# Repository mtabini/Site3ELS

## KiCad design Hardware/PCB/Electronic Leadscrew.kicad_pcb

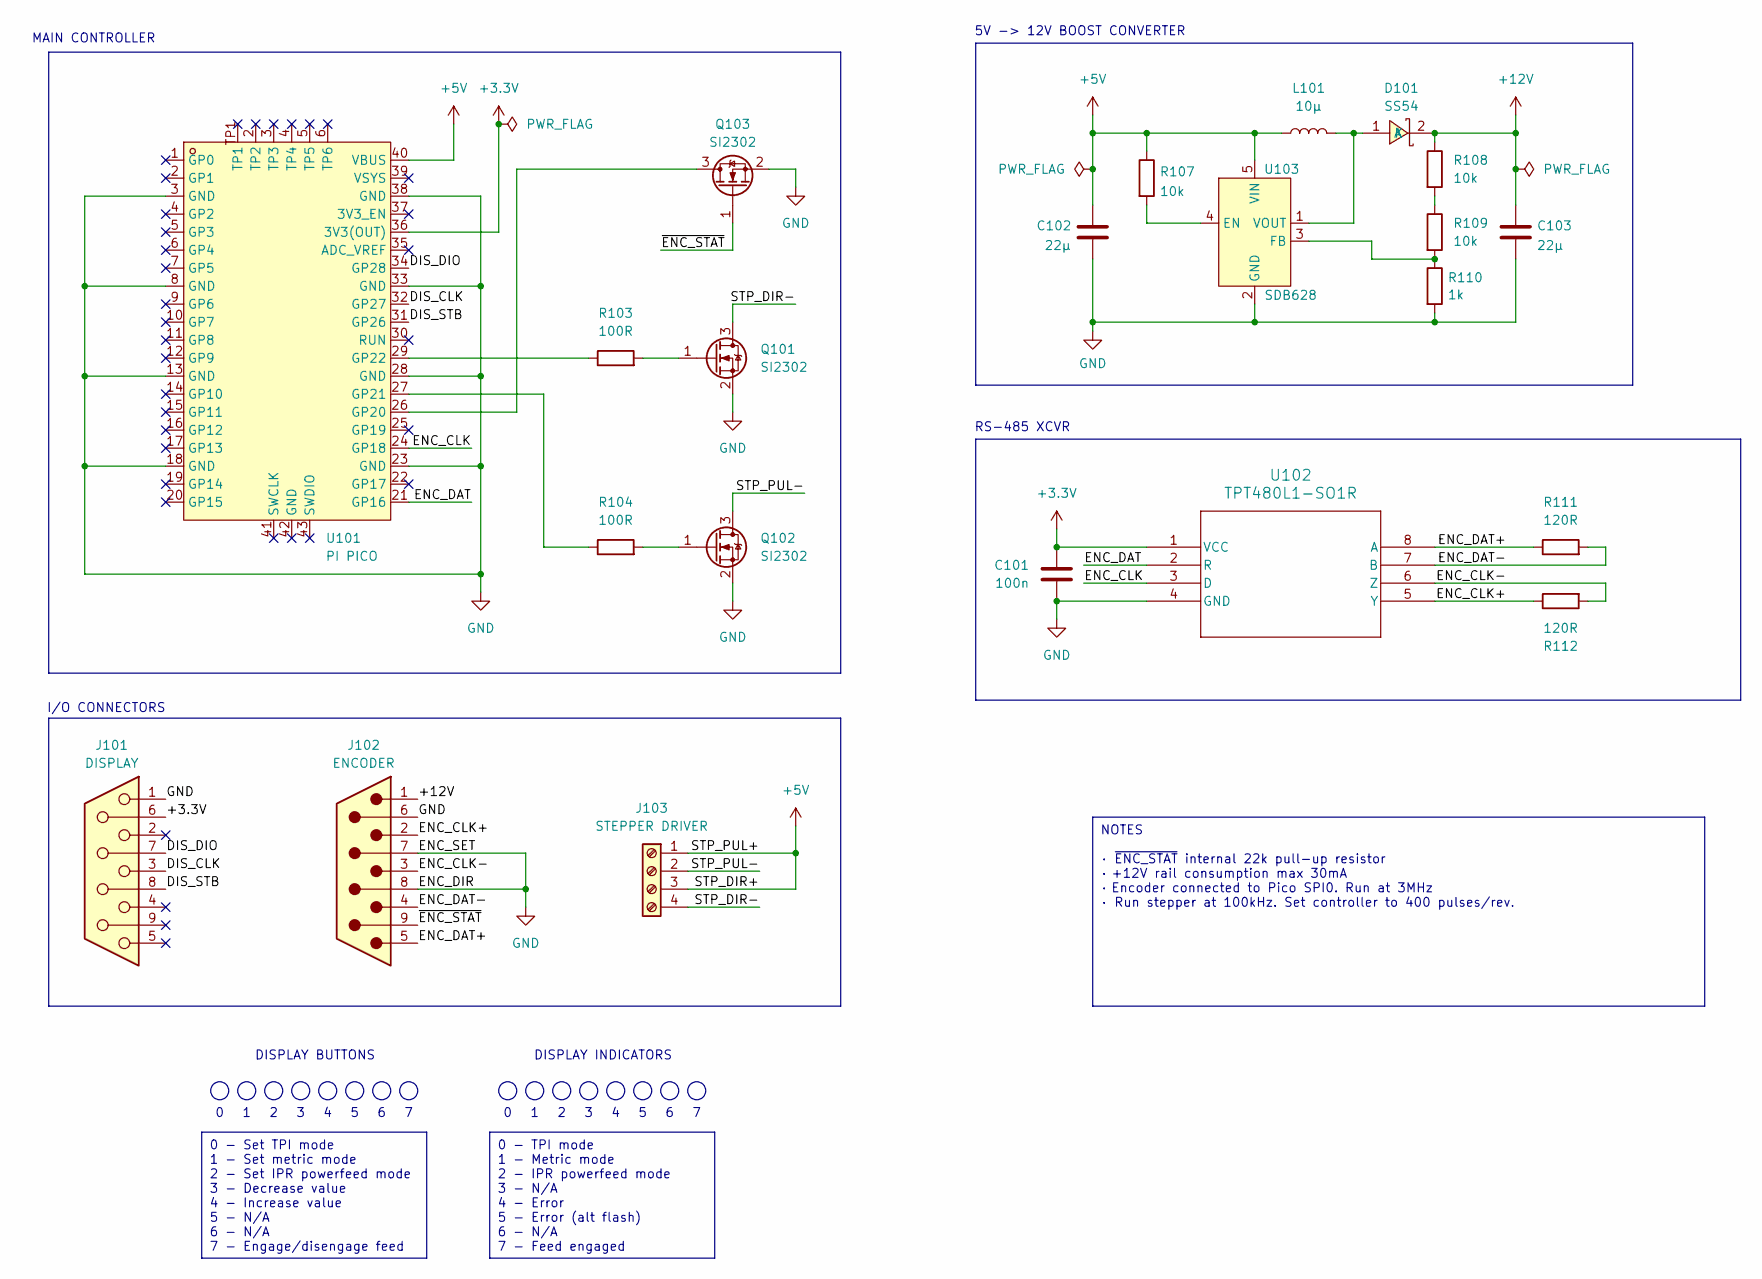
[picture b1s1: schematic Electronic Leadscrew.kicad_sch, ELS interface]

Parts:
C101: 100n; C_1206_3216Metric_Pad1.33x1.80mm_HandSolder; MPN C15008
C102, C103: 22µ; C_1206_3216Metric_Pad1.33x1.80mm_HandSolder
D101: SS54; SMA_L4.4-W2.8-LS5.4-R-RD; LCSC Part C22452
J101: DISPLAY; DSUB-9_Female_Horizontal_P2.77x2.84mm_EdgePinOffset7.70mm_H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
J102: ENCODER; DSUB-9_Male_Horizontal_P2.77x2.84mm_EdgePinOffset7.70mm_Hou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
J103: STEPPER DRIVER; TerminalBlock_4Ucon_1x04_P3.50mm_Horizontal
L101: 10µ; L_6.3x6.3_H3
Q101, Q102, Q103: SI2302; SOT-23_Handsoldering
R103, R104: 100R; R_1206_3216Metric_Pad1.30x1.75mm_HandSolder; MPN C17901
R107: 10k; R_1206_3216Metric_Pad1.30x1.75mm_HandSolder
R108, R109: 10k; R_1206_3216Metric_Pad1.30x1.75mm_HandSolder; MPN C17902
R110: 1k; R_1206_3216Metric_Pad1.30x1.75mm_HandSolder; MPN C4410
R111, R112: 120R; R_1206_3216Metric_Pad1.30x1.75mm_HandSolder
U101: PI PICO; COMM-SMD_L51.0-W21.0-P2.54_SC0916; LCSC Part C7203002
U102: TPT480L1-SO1R; SO1SOP-8-A_TPK
U103: SDB628; SOT-23-6_Handsoldering

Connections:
+3.3V: C101.1, J101.6, U101.36 (3V3(OUT)), U102.1 (VCC)
+5V: C102.1, J103.1, J103.3, L101.1, R107.1, U101.40 (VBUS), U103.5 (VIN)
+12V: C103.1, D101.2 (K), J102.1, R108.1
/DIS_CLK: J101.3, U101.32 (GP27)
/DIS_DIO: J101.7, U101.34 (GP28)
/DIS_STB: J101.8, U101.31 (GP26)
/ENC_CLK: U101.24 (GP18), U102.3 (D)
/ENC_CLK+: J102.2, R112.1, U102.5 (Y)
/ENC_CLK-: J102.3, R112.2, U102.6 (Z)
/ENC_DAT: U101.21 (GP16), U102.2 (R)
/ENC_DAT+: J102.5, R111.1, U102.8 (A)
/ENC_DAT-: J102.4, R111.2, U102.7 (B)
/STP_DIR-: J103.4, Q101.3 (D)
/STP_PUL-: J103.2, Q102.3 (D)
/~ENC_STAT: J102.9, Q103.1 (G)
GND: C101.2, C102.2, C103.2, J101.1, J102.6, J102.7, J102.8, Q101.2 (S), Q102.2 (S), Q103.2 (S), R110.2, U101.3 (GND), U101.8 (GND), U101.13 (GND), U101.18 (GND), U101.23 (GND), U101.28 (GND), U101.33 (GND), U101.38 (GND), U102.4 (GND), U103.2 (GND)
unnamed: D101.1 (A), L101.2, U103.1 (VOUT)
unnamed: Q101.1 (G), R103.2
unnamed: Q102.1 (G), R104.2
unnamed: Q103.3 (D), U101.26 (GP20)
unnamed: R108.2, R109.1
unnamed: R104.1, U101.27 (GP21)
unnamed: R103.1, U101.29 (GP22)
unnamed: R107.2, U103.4 (EN)
unnamed: R109.2, R110.1, U103.3 (FB)

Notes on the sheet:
0 - TPI mode 1 - Metric mode 2 - IPR powerfeed mode 3 - N/A 4 - Error 5 - Error (alt flash) 6 - N/A 7 - Feed engaged
NOTES · ~{ENC_STAT} internal 22k pull-up resistor · +12V rail consumption max 30mA · Encoder connected to Pico SPI0. Run at 3MHz · Run stepper at 100kHz. Set controller to 400 pulses/rev.
0 - Set TPI mode 1 - Set metric mode 2 - Set IPR powerfeed mode 3 - Decrease value 4 - Increase value 5 - N/A 6 - N/A 7 - Engage/disengage feed
MAIN CONTROLLER
DISPLAY INDICATORS
DISPLAY BUTTONS
5V -> 12V BOOST CONVERTER
I/O CONNECTORS
RS-485 XCVR

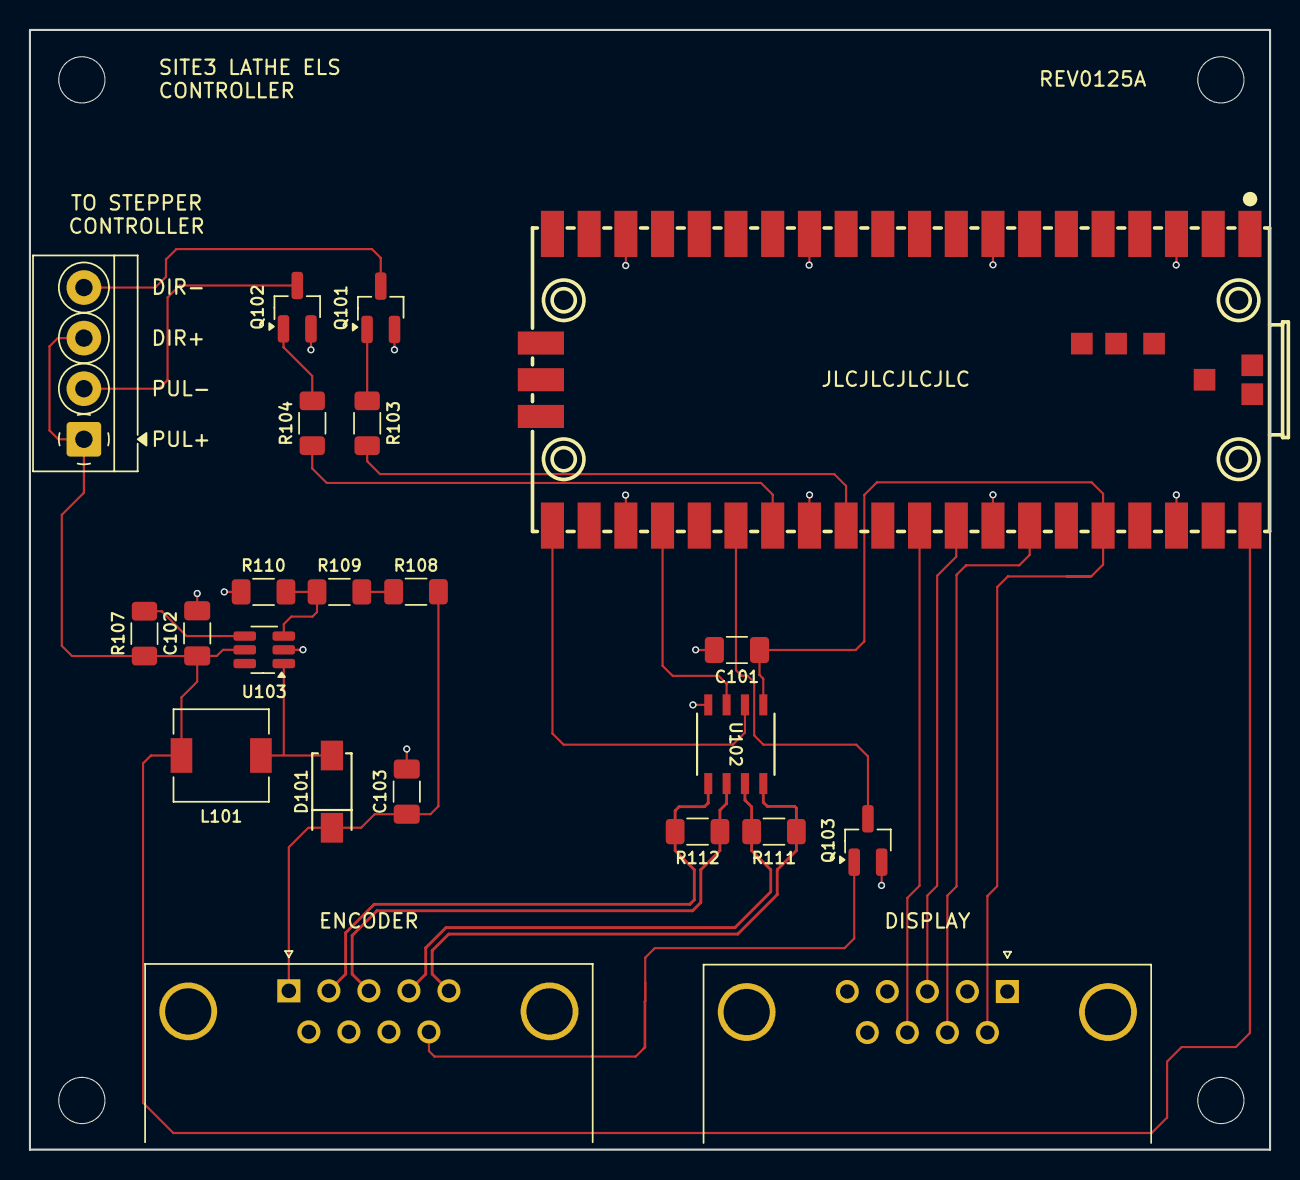
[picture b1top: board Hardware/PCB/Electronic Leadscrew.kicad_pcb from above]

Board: 2 copper layers, 85.8 x 77.5 mm, 22 parts (0 on the bottom side), 25 nets.

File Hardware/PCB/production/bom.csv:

Designator,Footprint,Quantity,Value,LCSC Part #
C101,1206,1,100n,C15008
"C102, C103",1206,2,22µ,
D101,SMA_L4.4-W2.8-LS5.4-R-RD,1,SS54,C22452
J101,DSUB-9_Female_Horizontal_P2.77x2.84mm_EdgePinOffset7.70mm_Housed_MountingHolesOffset9.12mm,1,DISPLAY,
J102,DSUB-9_Male_Horizontal_P2.77x2.84mm_EdgePinOffset7.70mm_Housed_MountingHolesOffset9.12mm,1,ENCODER,
J103,TerminalBlock_4Ucon_1x04_P3.50mm_Horizontal,1,STEPPER DRIVER,
L101,L_6.3x6.3_H3,1,10µ,
"Q101, Q102, Q103",SOT-23_Handsoldering,3,SI2302,
"R103, R104",1206,2,100R,C17901
R107,1206,1,10k,
"R108, R109",1206,2,10k,C17902
R110,1206,1,1k,C4410
"R111, R112",1206,2,120R,
U101,COMM-SMD_L51.0-W21.0-P2.54_SC0916,1,PI PICO,C7203002
U102,SO1SOP-8-A_TPK,1,TPT480L1-SO1R,
U103,SOT-23-6_Handsoldering,1,SDB628,

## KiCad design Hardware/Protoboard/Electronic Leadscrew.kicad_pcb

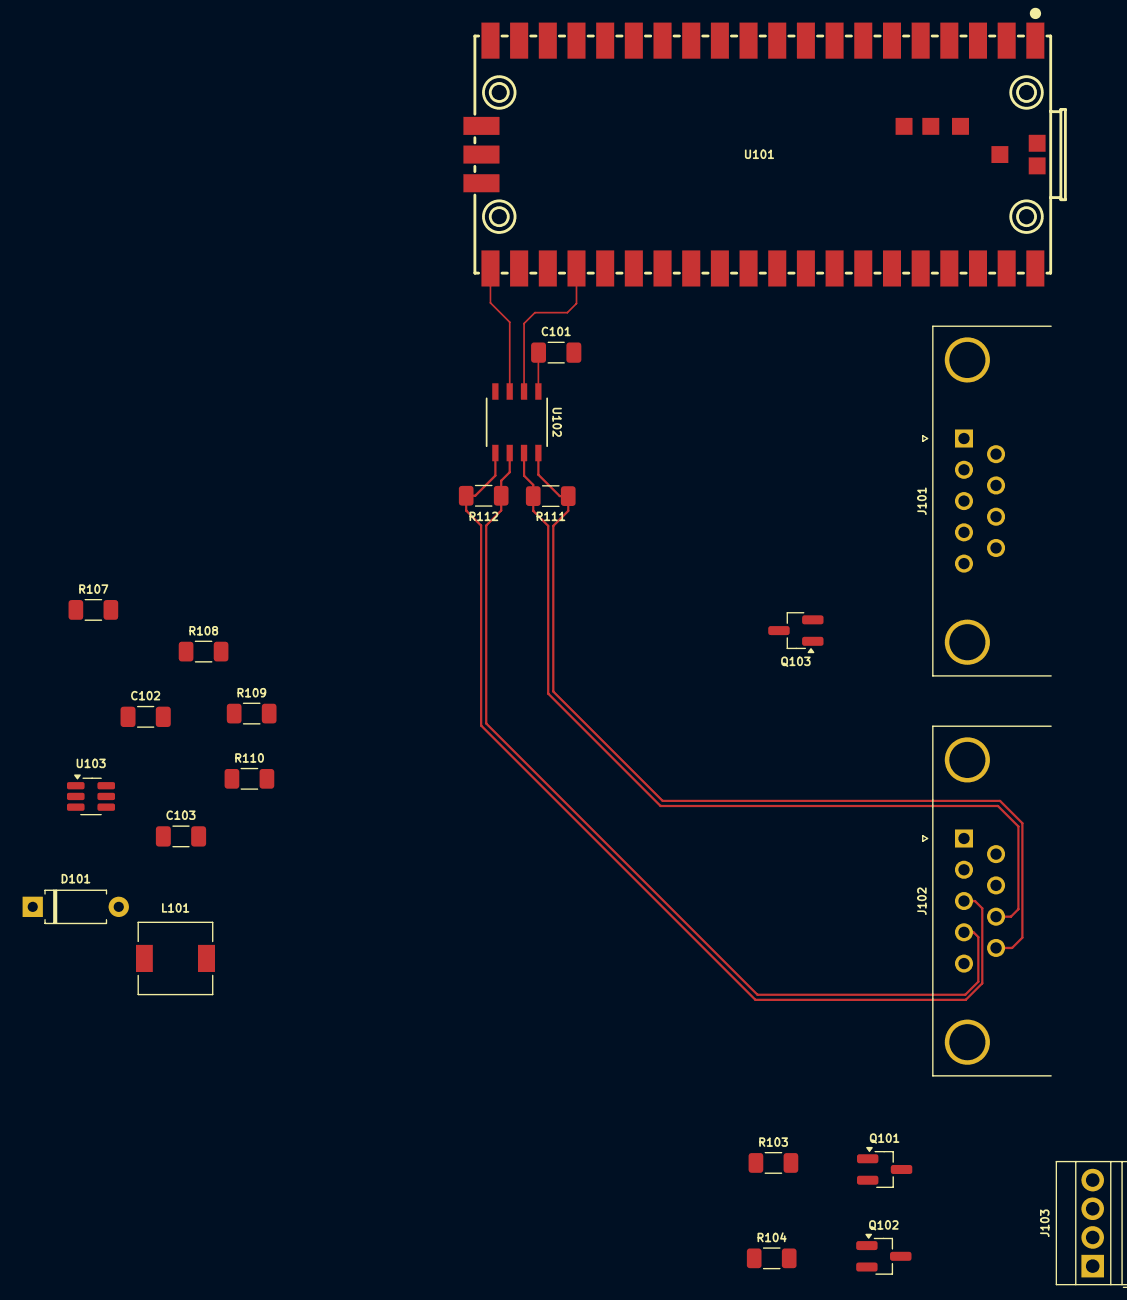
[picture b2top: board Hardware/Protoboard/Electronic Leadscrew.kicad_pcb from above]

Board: 2 copper layers, 22 parts (0 on the bottom side), 25 nets.

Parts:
C101: 100n; C_1206_3216Metric_Pad1.33x1.80mm_HandSolder
C102, C103: 22µ; C_1206_3216Metric_Pad1.33x1.80mm_HandSolder
D101: 1N5819; D_A-405_P7.62mm_Horizontal
J101: DISPLAY; DSUB-9_Female_Horizontal_P2.77x2.84mm_EdgePinOffset4.94mm_H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
J102: ENCODER; DSUB-9_Female_Horizontal_P2.77x2.84mm_EdgePinOffset4.94mm_H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
J103: STEPPER DRIVER; TerminalBlock_Xinya_XY308-2.54-4P_1x04_P2.54mm_Horizontal
L101: 10µ; L_6.3x6.3_H3
Q101, Q102, Q103: SI2302; SOT-23_Handsoldering
R103, R104: 100R; R_1206_3216Metric_Pad1.30x1.75mm_HandSolder
R107, R108, R109: 10k; R_1206_3216Metric_Pad1.30x1.75mm_HandSolder
R110: 1k; R_1206_3216Metric_Pad1.30x1.75mm_HandSolder
R111, R112: 120R; R_1206_3216Metric_Pad1.30x1.75mm_HandSolder
U101: PI PICO; COMM-SMD_L51.0-W21.0-P2.54_SC0916
U102: TPT480L1-SO1R; SO1SOP-8-A_TPK
U103: SDB628; SOT-23-6_Handsoldering

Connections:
+3.3V: C101.1, J101.6, U101.36 (3V3(OUT)), U102.1 (VCC)
+5V: C102.1, L101.1, R107.1, U101.40 (VBUS), U103.5 (VIN)
+12V: C103.1, D101.1 (K), J102.1, R108.1
/DIS_CLK: J101.3, U101.32 (GP27)
/DIS_DIO: J101.8, U101.34 (GP28)
/DIS_STB: J101.7, U101.31 (GP26)
/ENC_CLK: U101.21 (GP16), U102.3 (D)
/ENC_CLK+: J102.3, R112.1, U102.5 (Y)
/ENC_CLK-: J102.4, R112.2, U102.6 (Z)
/ENC_DAT: U101.24 (GP18), U102.2 (R)
/ENC_DAT+: J102.9, R111.1, U102.8 (A)
/ENC_DAT-: J102.8, R111.2, U102.7 (B)
/STP_DIR-: J103.4, Q101.3 (D)
/STP_PUL-: J103.2, Q102.3 (D)
/~ENC_STAT: J102.5, Q103.1 (G)
GND: C101.2, C102.2, C103.2, J101.2, J102.2, Q101.2 (S), Q102.2 (S), Q103.2 (S), R110.2, U101.3 (GND), U101.8 (GND), U101.13 (GND), U101.18 (GND), U101.23 (GND), U101.28 (GND), U101.33 (GND), U101.38 (GND), U102.4 (GND), U103.2 (GND)
unnamed: D101.2 (A), L101.2, U103.1 (VOUT)
unnamed: Q101.1 (G), R103.2
unnamed: Q102.1 (G), R104.2
unnamed: Q103.3 (D), U101.29 (GP22)
unnamed: R108.2, R109.1
unnamed: R104.1, U101.26 (GP20)
unnamed: R103.1, U101.27 (GP21)
unnamed: R107.2, U103.4 (EN)
unnamed: R109.2, R110.1, U103.3 (FB)

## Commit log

2024-11-28 Initial commt
2024-11-28 Change microstepping settings
2024-11-28 Update schematics
2025-01-22 Add sleep and keyboard input guards
2025-01-23 Update PCB
2025-02-22 Refactor display speed handling and update configuration for stepper pins
